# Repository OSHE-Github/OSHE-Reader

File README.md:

# **OSHE-Reader Spring 2026 Report**

Ian Mitchell, Riley Patterson, Owen Dodson, Ian Ranstadler, Alycia Greer  
---

# **Description**

OSHE-Reader is an open-source e-reader device capable of displaying text from the EPUB and PDF E-book file formats. This project’s goal is to create a cheaper alternative to products from companies like Amazon and Kobo. It will stay open to the public, using free and open source software like LVGL, Github, EEZ Studio and Arduino IDE, allowing more collaboration and easy uploading of books, compared to other e-readers that require workarounds to upload custom content.

# **Methodology**

### **Overview**

The design of the OSHE-Reader is loosely based on the previous work of Joey Castillo’s *The Open Book* \[1\] and atomic14’s *ESP32 Based ePub Reader* \[2\]. The former was designed as a very basic implementation of an e-reader, with the main goal of being easily manufacturable by an end-user. Unfortunately, this goal came at the expense of quality, with the design being stripped down to bare essentials, both on the hardware side, lacking a proper case, using AAA batteries, as well as the software side only supporting raw text file formats. Atomic14’s design incorporates much more complicated features, especially on the software side with .epub file parsing for standard e-book reading capabilities, however this design was not made for end users, is lacking a case, and has limited e-paper screen support. The OSHE-Reader attempts to solve problems in these prior open source e-readers by creating an open source e-reader with full functionality, principled design choices, and most importantly: a simple and consistent experience for an end user.

The OSHE-Reader’s design falls largely into three categories: electrical, firmware, and hardware. The design considerations of these three categories are discussed in further detail below.

### **Electrical**

#### **Battery**

In order to be a device capable of being used portably, the OSHE-Reader needed to use some form of battery, such that the device could store energy and be used while not directly plugged in. For this system, we chose lithium polymer (LiPO) batteries for their slim profile and ability to be recharged. The choice to use a LiPO battery to power the device provides the best features in energy storage density and internal recharging, though at the cost of increased complexity relative to consumer AAA batteries, which require less surrounding systems to function, though are bulkier, heavier, and need to be removed to be recharged.

In order to recharge our LiPO batteries, two systems are necessary: a method of power connection as a source of power from which the battery can be charged, and a charging integrated chip (IC) which can handle the complex recharging process.

#### **Battery Charging**

To handle the power connection system, we decided on using the existing USB-C port. This port provides a consistent, readily available connector that works with a variety of existing cables, such as those used for charging phones or plugging in peripheral devices like computer mice and keyboards. This USB-C port is currently only used for charging, and as such requires minimal components, while allowing the e-reader to consume up to 1.5A of current, well above the requirements of the device. This device’s USB-C port was designed with the USB Implementers Forum’s guidelines on USB-C devices in consideration, and should stand up to the requirements for certification \[3\], though that is not something this project will be doing.

Regarding the second system required for the chosen LiPO batteries, the BQ2057CSNTR from Texas Instruments was chosen as our battery charging IC. The BQ2057CSNTR is an older battery charging chip, but was chosen primarily for its package. Because the BQ2057CSNTR comes packaged as a SOIC-8, the IC can be hand-soldered, which greatly reduces the barrier of entry for end users attempting to create their own OSHE-Reader. This however poses additional challenges, as the BQ2057CSNTR is lacking in some features, most notably of which is the lack of a power path feature, which means that the BQ2057CSNTR cannot, on its own, support using a device while simultaneously charging. This issue can be circumvented with the addition of a load-sharing system \[4\]. With this load-sharing system, the OSHE-Reader can now be used while charging.

#### **Buck Converter**

The LiPO battery outputs a voltage of 3.7 volts, but our screen and microcontroller run on 3.3 volts. To make sure we would be able to run both devices safely, we decided to add a buck converter to the circuit. The buck converter we picked is the TPS5432. The primary factor behind this choice was its package size, similar to our choice with the battery charging IC. By allowing it to be easily hand-solderable, such as with the SOIC-8 packaging type, it keeps our device available to more at-home builders. This device also helps keep the other components safe, as when it's running, any voltage too high, around \~4.3 volts, will cause a break, and it will need to be reset, and any value less than \~3.3 volts also puts the device in the same state. This additional protection helps make sure the user will not accidentally fry any parts they are using.

#### **Microcontroller**

For the OSHE-Reader, a core processing unit is necessary to do the computation required for the parsing and displaying of e-books. Because our device is battery-powered, a lower power microcontroller greatly increases the lifespan of our device. We selected the ESP32-C6 to be a featureful, yet low-power device that is readily available for hobbyists. ESP-IDF and Arduino IDE support the ESP32-C6 so development would also be easier. Flash size was a factor in selecting a microcontroller and the C6’s 8MB flash memory would be able to hold screen buffers. Furthermore, the C6 has a lot of sleep modes to limit power consumption while idle. Deep sleep in particular will be useful for the device in an “off state” where it can still wake up or refresh the screen periodically.

#### **Micro SD Card**

In order to be able to upload files to the OSHE Reader, an SD card reader was needed to provide EPUB files to the device. For this purpose, an SD card reader slot was chosen for our design. We chose to use a Push-Push mechanism for our SD card reader, since that would allow easier removal of the SD card from the slot in our case design, allowing the user to simply push the card inwards again and have it pop out, clear of the case, rather than needing to grab the device and pull it outwards from the inside of the case.

#### **User Input**

As described below in the GUI and Case Design sections, the OSHE-Reader will have five buttons (4 directions, 1 select). Each of these buttons must be connected to a GPIO pin on the microcontroller. Each of the buttons is pulled down to ground, such that the buttons are active high.

#### **Display**

The most user-facing component of the electrical system of the OSHE-Reader is the display. There is an enormous number of choices for potential displays, however the unique use case of displaying black and white book pages, which change fairly infrequently, means e-readers are particularly suited to e-paper displays. E-paper display technology is a relatively new display technology that trades refresh speed and color density for extreme power efficiency. We chose a Waveshare 5.83” 648 x 480 pixel display with 1-bit color depth as our e-paper display. We chose this display primarily because of its general availability and documentation, additionally, Waveshare has an ESP32 e-paper display driver board, which we used to verify our screen. This e-paper display uses a 4-wire SPI connection which is easy to implement on the microcontroller, however the display requires high voltages to operate, and thus needs an external boost converter. For our implementation we looked at the Waveshare driver board’s open source schematics and implemented a similar option \[5\].

#### **Printed Circuit Board**

For the design of our Circuit board, we wanted the vast majority of components to be hand solderable on our board. For this reason, most of our components are surface mount with a size of 1206, which is on the larger side of surface mount components.

### **Firmware**

#### **Micro SD Card**

#### In order to read from and write to an SD card, we imported the arduino SD card library (SD.h), which provides low level functionalities. However, in order to extract compressed files from an epub (zip archive), we needed access to a posix-style file system. To solve this problem, we employed the arduino-posix-fs library \[6\], which provides stdio functions (notably fopen, fclose, fread, and fwrite) which emulate the stdio.h functions found in a unix operating system.

#### **User Input**

#### To give the microcontroller the ability to read user input we must first enter the Arduino IDE again. We will connect pins from the microcontroller to certain functions that we will use in the e-reader GUI. Using the library OneButton \[7\] by mathertel, we were able to successfully debounce the buttons for single-press applications. This library is promising for future long-press implementations, such as turning on/off the device. Explicit button labels in the GUI allow for the user input to move to a new screen directly as opposed to moving around the screen to select an option. The buttons are responsive for the user and LVGL.

#### **EPUB File Processing**

In order to process an EPUB file from a zip archive to formatted text, three main steps need to be taken. Firstly, the archives files need to be extracted and uncompressed, then the archive needs to be parsed using an xml parser to extract the structural information about the contents of the EPUB, then finally, a word wrapping algorithm can be applied to format the raw text into a single page worth of text.

##### **EPUB File Unzipping**

The first step in the processing of an EPUB file is the decompression and extraction of the contents of the EPUB. To do this, we needed a library that could handle not only the decompression, but also have the necessary extensions for the archive support.

Many libraries supported the simple compression and decompression algorithms of the zip format, but only the miniz library \[8\] had support for the archive extensions, which provide an API for viewing the individual files in an archive, extracting them individually, and decompressing them.

Unfortunately, this library’s archive functions required the inclusion of the stdio header, which typically provides file read and write functionality on an operating system, however, working within the Arduino ecosystem, we had no operating system or file system. Therefore, we had to use the previously mentioned arduino-posix-filesystem library. While this substitution appeared to be successful, overall the integration of miniz into an embedded platform was unsuccessful, with the library still failing to function as of the end of the semester.

##### **EPUB File Parsing**

#### Parsing an EPUB requires extracting information from a few key files. The container file gives the location of the contents file. The contents file gives metadata (author, title, book language), locations of pages as xhtml files, the table of contents, and the spine. The table of contents includes all the chapters and a unique id attached to each.

Using Expat, the XML parser chosen last semester for its functionality with limited memory/processing power, we can parse this chain of files to gather all the relevant information on a book. Using the chapter ids from the table of contents and header tags in XML, we can locate the start of new chapters, and begin parsing them based on the paragraph tags. 

As we extract paragraphs, they will be sent to the pagination algorithm in chunks to be formatted on the screen. As the paragraphs are sent, we can keep track of where we left off in a chapter to maintain a kind of bookmark, as well as making the pages smoother if you close and reopen a book.

##### **Pagination and Word Wrapping**

For displaying the book for the user to view, we need a way to format the text while keeping count of pages. By taking the paragraphs from the file and formatting them to break the section of text into lines and not cut off words, we used EEZ Studio to have textboxes that will automatically wrap the text and display the page the user is on.

#### **Display**

In order to display images to our e-paper display, we needed an appropriate driver to send commands and data to the e-paper controller board located on the display. Previously we had been successful in using our display’s provided firmware, however that code was poorly written and documented and was both missing features we needed, while having a lot of core functionality like SPI being written using basic GPIO pins rather than the onboard SPI hardware. In order to solve this problem the library was re-written, keeping only the core needed functionality such as: turning on, clearing, updating the image displayed, entering sleep mode, and turning off. This way, the library could be both smaller, saving space for the rest of the firmware, and also faster, by using the hardware SPI functions of our microcontroller rather than the GPIO pins.

#### **GUI Design**

The GUI design pivoted to using direct button to screen navigation. Due to the slow refresh rate of the screen, it was preferable to make one button press change a screen, instead of using a button press to navigate through moving menus. We wanted a simplistic and easy to navigate GUI to make the experience as smooth as possible. Explicit buttons help the user understand where a button press will go, eliminating ambiguity. Settings allow for more customization for the screen, such as dark mode. The library screen will be full of book selections and clicking a book will take you to the text in the file. The center button will have an explicit back button when applicable, taking the user to the previous screen they were at. We included marmot imagery to set up a recognizable, user-friendly “mascot” of sorts. 

#### **LVGL**

The Light and Versatile Graphics Library (LVGL) is an open source program/library that allows for easy GUI development. After discussing possible routes of GUI libraries we could use, we eventually settled on LVGL due to its documentation, compatibility with ESP32, and UI editor applications. EEZ studio was used to generate LVGL assets. EEZ studio allowed for easy implementation of groups, buttons, labels, and other custom actions. The design was created in a GUI that generates C code once settings were adjusted.

### **Hardware**

#### **Case Design**

To design the case we wanted to make sure it was optimized for as many people as possible. This can be difficult due to different hand sizes, but we tried to standardize it. To get feedback we created an initial case out of cardboard, and showed it to people asking them to fill out a google form. This allowed us to get feedback before we invested hours into an incorrectly designed case. Due to feedback, we slightly increased the size of the case, and added buttons to both sides of the case. This should mean that it is accessible for people both left and right handed, and that it sits comfortably in most people's hands. We kept all the buttons on the front of the screen (vs the side) because it keeps the electronic and case design simple, and from our feedback it is still easy to push with the thumb when the device is in standard operating condition. PLA and PETG were tested when printing the case design, both are suitable for the application \[11\].

#### **3D Model**

To house the device we decided to create a shell in Onshape, as it is an open source and relatively simple to use modeling software; for the situations that the user wanted to update the case. The model is split into 5 key parts, the front shell, back plate, battery holder, rocker buttons, and screen holder. The goal of the design is to create a case that has covered tactile buttons, ensuring a seamless look. The main center button will be a flush spring button built into the front panel. This design was partially inspired by an older nook button design. Due to ribbon cable location issues, the side buttons were changed to rocker buttons. The original plan of designing side buttons similarly to the center button proved impossible as there was no location where the buttons could exist without compromising the ribbon cable on the screen. The outcome was good, the separate print is not time or resource intensive and they feel great. All parts of the shell will be held together with M3 screws. By using screws instead of a snapping system, if the device gets dropped it will not split apart. Some feedback suggested a screw hole that does not travel through the entire back panel for structure so that change was made to the original design.

# **Progress in Previous Semester**

The past semester we started the schematic on the components for the PCB including USB-C Connector, Battery Charging, Buck Converter, Button Input, Display Connector, Micro SD Card Slot, and the Microcontroller. Testing the Buck Converter, Battery Charging, and the Microcontroller Input on breadboard to test the components to make sure the parts will work. On the software side we used the Arduino libraries to display the screen and LVGL to develop the GUI with an easy navigated menu. Looking into parsing and displaying an EPUB file on the e-reader. We also started to design a 3D printed case keeping in mind the button placement and how everything will be held in place.

# **Bill of Materials**

| Description | Part Number | Source | Unit Price | Qty | Cost |
| :---: | :---: | :---: | :---: | :---: | :---: |
| ESP32-C6 Devboard | 25723 | Waveshare | $7.29 | 1 | $7.29 |
| PCB | Rev 1 | JLCPCB | $35.40 | 1 | $35.40 |
| 4.22k Ohm Resistor | AC1206FR-074K22L | Digikey | $0.10 | 1 | $0.10 |
| 45.3k Ohm Resistor | RC1206FR-0745K3L | Digikey | $0.10 | 1 | $0.10 |
| 66.5k Ohm Resistor | RC1206FR-0766K5L | Digikey | $0.10 | 1 | $0.10 |
| 10k Ohm Resistor | RMCF1206FT10K0 | Digikey | $0.10 | 2 | $0.20 |
| 49.9 Ohm Resistor | TNPW120649R9BEEA | Digikey | $0.41 | 1 | $0.41 |
| 3.24k Ohm Resistor | RC1206FR-073K24L | Digikey | $0.10 | 1 | $0.10 |
| 5.1k Ohm Resistor | AC1206FR-075K1L | Digikey | $0.10 | 2 | $0.20 |
| 100k Resistor | RC1206FR-07100KL | Digikey | $0.10 | 8 | $0.80 |
| 1k Resistor | RMCF1206FT1K00 | Digikey | $0.10 | 1 | $0.10 |
| 8.2 nFarad Capacitor | CC1206JKNPOZBN822 | Digikey | $0.47 | 1 | $0.47 |
| 82 pFarad Capacitor | CC1206JRNPOBBN820 | Digikey | $0.19 | 1 | $0.19 |
| 10 nFarad Capacitor | C1206C103K2RECTU | Digikey | $0.18 | 1 | $0.18 |
| 470 pFarad Capacitor | VJ1206A471JXGTW1HV | Digikey | $0.14 | 1 | $0.14 |
| 22 uFarad Capacitor | CL31A226KAHNNNE | Digikey | $0.08 | 2 | $0.16 |
| 0.1 uFarad Capacitor | C1206C104K5RACTU | Digikey | $0.08 | 6 | $0.48 |
| 10 uFarad Capacitor | CL31A106KBHNNNE | Digikey | $0.08 | 3 | $0.24 |
| 4.7 uFarad Capacitor | CL31B475KAHNNNE | Digikey | $0.16 | 2 | $0.32 |
| 1u/50V Farad Capacitor | C3216X7R1H105K160DB | Digikey | $0.24 | 7 | $1.68 |
| PNP BJT | PZT751T1G | DigiKey | $0.63 | 1 | $0.63 |
| BQ2057CSNTR | BQ2057CSNTR | Digikey | $3.87 | 1 | $3.87 |
| IRF7326D2TRPBF | IRF7326D2TRPBF | Digikey | $0.63 | 1 | $0.63 |
| 2.2 uHenries Inductor | AIML-1206-2R2K-T | Digikey | $0.21 | 1 | $0.21 |
| TPS5432DDA | TPS5432DDA | Digikey | $0.96 | 1 | $0.96 |
| Push Buttons | PTS636SM43SMTR LFS | Digikey | $0.20 | 5 | $1.00 |
| MBR0530 | MBR0530 | Digikey | $0.31 | 3 | $0.93 |
| Sil308EDL | SI1308EDL-T1-GE3 | Digikey | $0.58 | 1 | $0.58 |
| 10 u/1A Henries Inductor | CC453232A-100KL | Digikey | $0.40 | 1 | $0.40 |
| 112L-TDA0 | 112L-TDA0 | Digikey | $3.44 | 1 | $3.44 |
| CUHZ5V6\_H3F Diode | CUHZ5V6,H3F | Digikey | $0.44 | 1 | $0.44 |
| PPTC Polyfuse | 0ZCJ0050FF2G | Digikey | $0.20 | 2 | $0.40 |
| Thermistor | B57550G1103F000 | Digikey | $3.11 | 1 | $3.11 |
| LED | HSMY-C110 | Digikey | $0.29 | 1 | $0.29 |
| 2k Ohm Resistor | RC1206FR-132KL | Digikey | $0.10 | 1 | $0.10 |
| JST Connector | S2B-PH-K-S | Digikey | $0.10 | 1 | $0.10 |
| USB-C Connector | 2171750001 | Digikey | $0.75 | 1 | $0.75 |
| Test Point | S1751-46R | Digikey | $0.24 | 20 | $4.72 |
| Ribbon Cable Connector | FH12A-24S-0.5SH(55) | Digikey | $1.65 | 2 | $3.30 |
| 6.8k Resistor | ERA-8AEB682V | Digikey | $0.24 | 2 | $0.48 |
| 0.47 Resistor | KDV12DR470ET | Digikey | $0.28 | 1 | $0.28 |
| 0.2 Ohm Shunt Resistor | WSL2512R2000FEA | Digikey | $0.65 | 2 | $1.30 |

## **E-Reader Cost Breakdown **
**

# **Tools Used**

| Category  | Item  | Part Number | Source | Cost |
| :---- | :---- | :---- | :---- | :---- |
| Hardware | Breadboard  | PRT-12615 | SparkFun Electronics | $7.75 |
|  | Multimeter  | 167 | Fluke | $260.00 |
|  | Oscilloscope  | DSOX2004A | Newark | $3306.90 |
|  | Solder Iron | Hakko FX888Dx | Equipment | $121.47 |
| Software | Google Slides | N/A | Google | Free |
|  | LVGL | N/A | LVGL LLC | Free |
|  | Arduino IDE | N/A | Qualcomm Technologies, Inc. | Free |
|  | EEZ Studio | N/A | Envox Experimental Zone | Free  |
|  | KiCAD | N/A | KiCAD | Free |
|  | OnShape | N/A | PTC Inc. | Free |

# **Part Assembly**

### **PCB**

The circuit schematic and Circuit Board were both designed using KiCAD, a free open source software for circuit and circuit board design. The PCB was designed to be hand solderable while also not taking up a lot of space within the case to allow for the battery to take up the rest of the available space. Doing it this way would allow consumers to hand solder boards without the need of solder paste or reflow oven, while the size would allow the device to keep a slimmer profile making it more comfortable to hold. To achieve this, most of the components were surface mounted with a package size of 1206\. These components were easily soldered with a standard soldering iron heated to 470 degrees centigrade. Some components were not available in the 1206 package size that we wanted so these parts were soldered using reflow techniques. 

Future revisions of the Circuit Board should focus on a redesign of the device to allow for a smaller board to be created. There was also a need to add a schottky diode to our BJT to prevent backfeeding through Resistor 5 to allow for our battery charger to receive the voltage it needs to function properly.

#### **Display Connector**

The Display connector needs to adapt a fine pitch FPC cable with 0.5mm pitch, thus the connector component also has a 0.5mm pin pitch. For this reason, the display connector was not hand soldered and was instead soldered using reflow techniques in the interest of saving time. This had varying levels of success as this caused the contacts to bridge. Attempts to remove the display connector were made, but resulted in the removal of pads and traces connected to it. On a second attempt, the display connector was soldered to the board with a mixture of reflow and hand soldering techniques. This attempt did not result in bridged contacts and the display connector could be used.

#### **Buck Converter**

The design for the buck converter was borrowed from a design made by Texas Instruments as it was a proven design that utilized most of the parts already implemented in the schematic. The buck converter was then isolated from other components on the board due to the noise it creates, with all other components being routed around it.

#### **SD Card Slot**

The SD card reader was also only available in a package size smaller than 1206, however it was bigger than the package size for the display connector. This does mean that the SD Card reader is hand solderable given enough time and patience. However, it was reflow soldered for the sake of time.

### **Case**

All case pieces must be 3D-printed, which includes the front panel, back panel, screen bracket, two side buttons, and the battery bracket. The case has been tested in both PLA and PETG, both are suitable \[11\]. To assemble, start by placing the PCB on the bottom standoffs of the rear panel, aligning them with the screw holes. Plug in the battery to the PCB and fit inside the battery bracket. Align the battery bracket with the top standoffs of the rear panel, facing the battery downwards. The PCB and battery bracket should lay somewhat flush with each other. Attach the screen to the PCB via the ribbon cable and put the screen in the screen bracket. Set the screen bracket on top of the four standoffs, aligning them with the screw holes. For the front panel, align the side buttons with the holes on the front case. Flip over the front case with your figures holding the buttons in place or set the buttons on top of the PCB, facing you. Finally, place the top panel on top of the rest of the assembly and use four M3x14mm screws to close the case. Screw in the screws until there is a resistance of it hitting the back of the rear panel. The back of the case should be flush with no screw protrusions.

# **Characteristic Data**

The above graph shows an example of our safe battery charging circuit. On the horizontal axis the duration of the charging cycle is displayed in minutes, and on the vertical axis, the battery’s voltage level. During a charging cycle, the battery charging chip will start the battery in current regulation mode, where a set amount of current (\~100mA for our design) is driven into the battery, once a voltage threshold is reached, the battery charger initiates the voltage regulation mode, where the charging voltage is instead held steady and the charging current gradually decreases (not pictured). Finally, after the charging current reaches a minimum threshold, all charging stops automatically to prevent overcharging, at which point the battery is fully charged.

# **References**

| \[1\] | GitHub \- atomic14/diy-esp32-epub-reader: ESP32 Based ePub Reader [https://github.com/atomic14/diy-esp32-epub-reader](https://github.com/atomic14/diy-esp32-epub-reader) |
| :---- | :---- |
| \[2\] | GitHub \- joeycastillo/The-Open-Book: The Open Book: Project Reboot [https://github.com/joeycastillo/The-Open-Book](https://github.com/joeycastillo/The-Open-Book)  |
| \[3\] | USB Type-C® Cable and Connector Specification Release 2.4 [https://usb.org/document-library/usb-type-cr-cable-and-connector-specification-release-24](https://usb.org/document-library/usb-type-cr-cable-and-connector-specification-release-24) |
| \[4\] | Designing A Li-Ion Battery Charger and Load Sharing System With Microchip’s Stand-Alone Li-Ion Battery Charge Management Controller [https://ww1.microchip.com/downloads/en/AppNotes/01149c.pdf](https://ww1.microchip.com/downloads/en/AppNotes/01149c.pdf) |
| \[5\] | E-Paper ESP32 Driver Board V3 Schematic [https://files.waveshare.com/wiki/E-Paper-ESP32-Driver-Board/E-Paper\_ESP32\_Driver\_Board\_V3.pdf](https://files.waveshare.com/wiki/E-Paper-ESP32-Driver-Board/E-Paper_ESP32_Driver_Board_V3.pdf) |
| \[6\] | Arduino POSIX Filesystem Library [https://github.com/pschatzmann/arduino-posix-fs](https://github.com/pschatzmann/arduino-posix-fs) |
| \[7\] | OneButton Button Press Library [https://github.com/mathertel/OneButton](https://github.com/mathertel/OneButton) |
| \[8\] | Miniz (z-lib replacement) Library [https://github.com/richgel999/miniz](https://github.com/richgel999/miniz) |
| \[9\] | ESP32: Guide for MicroSD Card Module using Arduino IDE [https://randomnerdtutorials.com/esp32-microsd-card-arduino/](https://randomnerdtutorials.com/esp32-microsd-card-arduino/) |
| \[10\] | \[ESP32 & LVGL\] How to Use a Button as an Input for UI Control\!: [https://www.youtube.com/watch?v=Lp2\_MLgs7d0](https://www.youtube.com/watch?v=Lp2_MLgs7d0) |
| \[11\] | PETG vs PLA vs ABS: 3D Printing Strength Comparison [https://ultimaker.com/learn/petg-vs-pla-vs-abs-3d-printing-strength-comparison/](https://ultimaker.com/learn/petg-vs-pla-vs-abs-3d-printing-strength-comparison/) |
| \[12\] | Texas Instruments Buck Converter design [https://www.ti.com/lit/ds/symlink/tps5432.pdf](https://www.ti.com/lit/ds/symlink/tps5432.pdf) |

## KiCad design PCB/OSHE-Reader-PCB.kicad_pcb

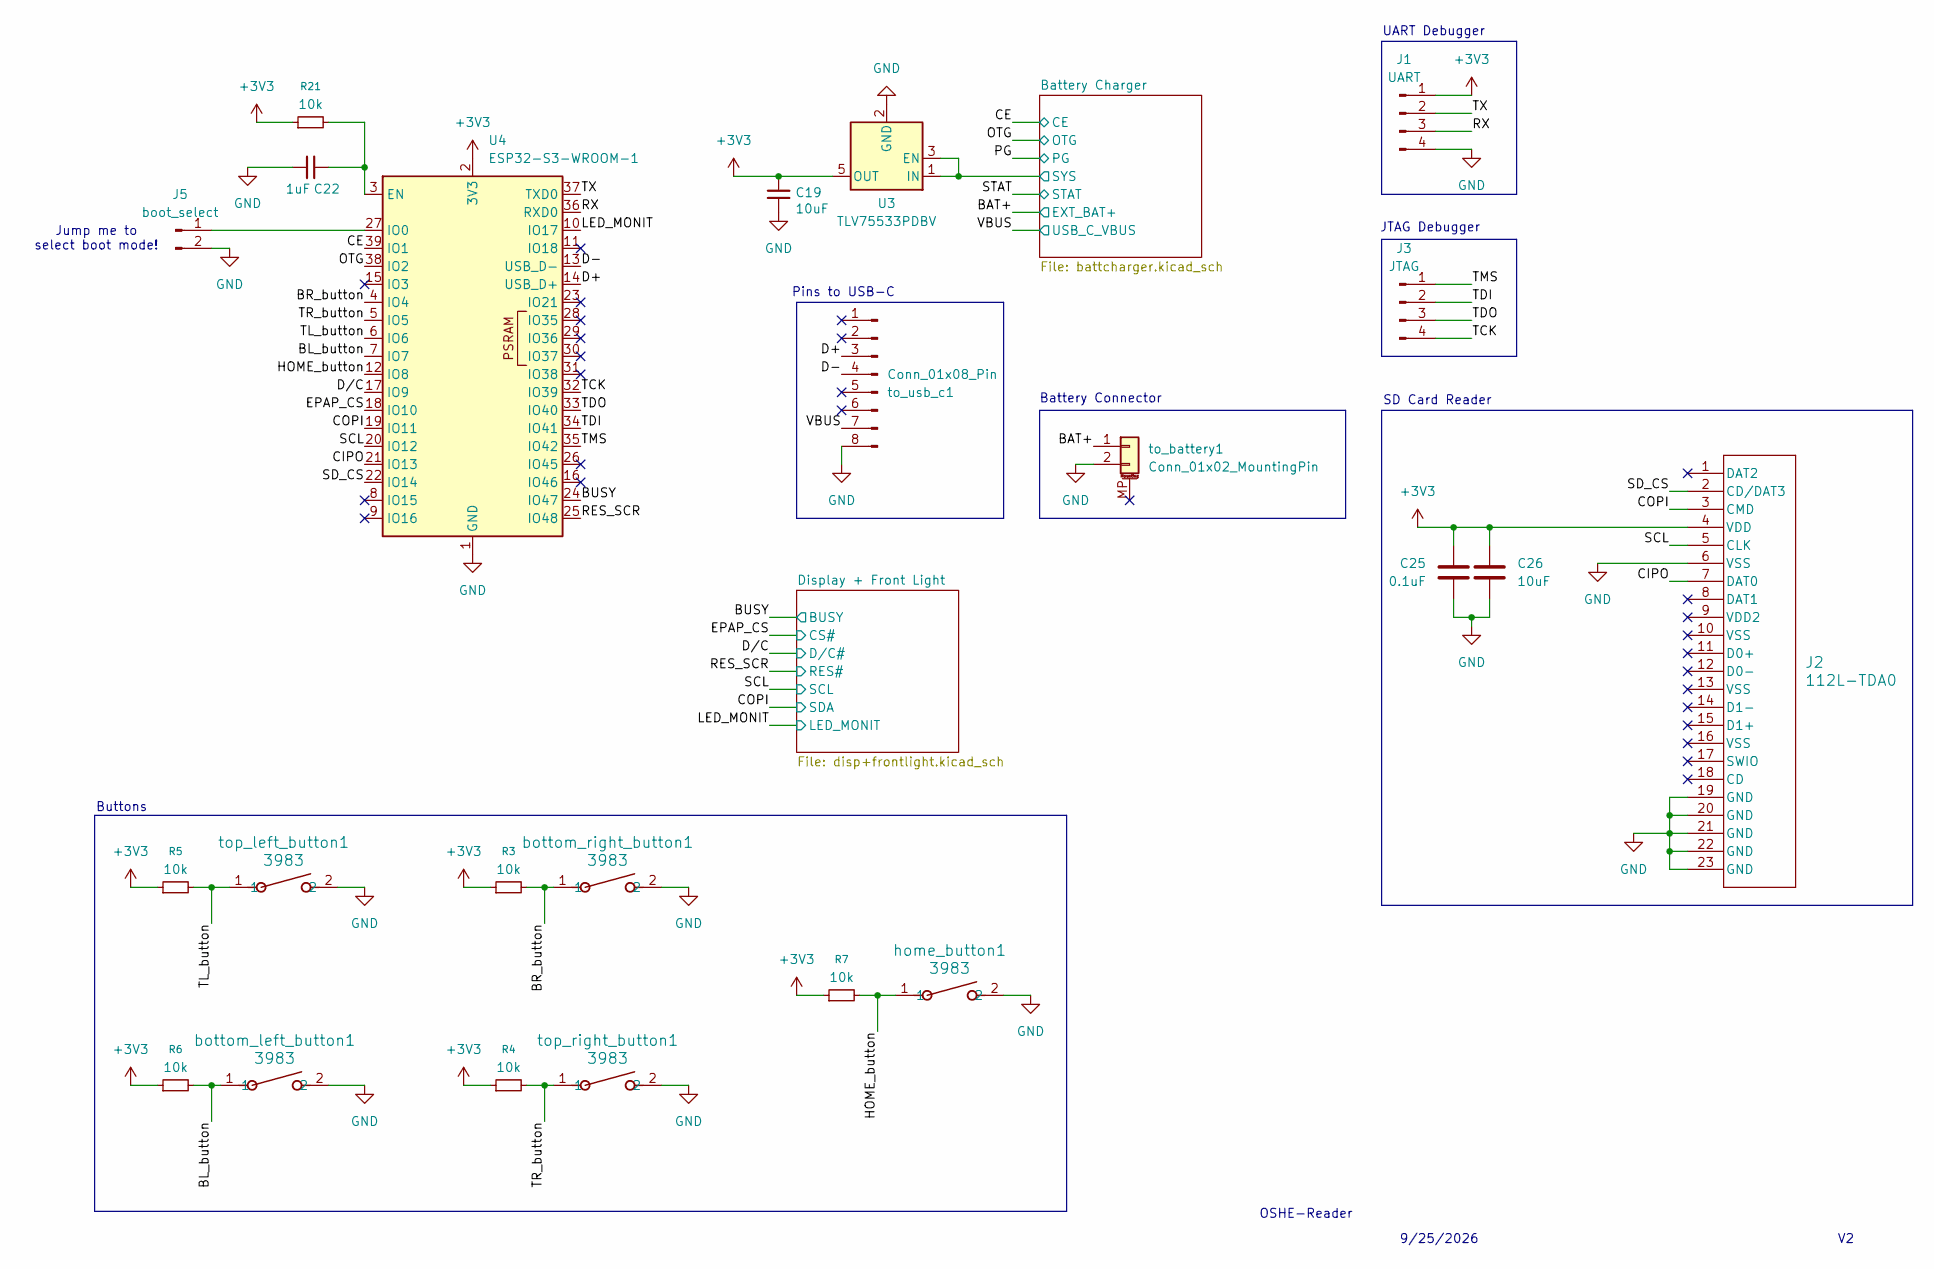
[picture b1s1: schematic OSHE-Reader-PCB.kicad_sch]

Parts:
C19: 10uF; C_1206_3216Metric_Pad1.33x1.80mm_HandSolder
C22: 1uF; L_1206_3216Metric_Pad1.22x1.90mm_HandSolder
C25: 0.1uF; C_1206_3216Metric
C26: 10uF; C_1206_3216Metric
J1: UART; PinHeader_1x04_P2.54mm_Vertical
J2: 112L-TDA0; CONN_112L-TDA0_ATT
J3: JTAG; PinHeader_1x04_P2.54mm_Vertical
J5: boot_select; PinHeader_1x02_P2.54mm_Vertical
R3, R4, R5, R6, R7, R21: 10k; R_1206_3216Metric_Pad1.30x1.75mm_HandSolder
U3: TLV75533PDBV; SOT-23-5
U4: ESP32-S3-WROOM-1
bottom_left_button1: 3983; SW_3983_ADA
bottom_right_button1: 3983; SW_3983_ADA
home_button1: 3983; SW_3983_ADA
to_battery1: Conn_01x02_MountingPin; JST_PH_S2B-PH-SM4-TB_1x02-1MP_P2.00mm_Horizontal
to_usb_c1: Conn_01x08_Pin; PinHeader_1x08_P2.54mm_Vertical
top_left_button1: 3983; SW_3983_ADA
top_right_button1: 3983; SW_3983_ADA

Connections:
+3V3: C19.1, C25.1, C26.1, J1.1, J2.4 (VDD), R3.1, R4.1, R5.1, R6.1, R7.1, R21.1, U3.5 (OUT), U4.2 (3V3); also elsewhere on the board
/BAT+: to_battery1.1; also elsewhere on the board
/BL_button: R6.2, U4.7 (IO7), bottom_left_button1.1
/BR_button: R3.2, U4.4 (IO4), bottom_right_button1.1
/BUSY: U4.24 (IO47); also elsewhere on the board
/Battery Charger/SYS: U3.1 (IN), U3.3 (EN); also elsewhere on the board
/CE: U4.39 (IO1); also elsewhere on the board
/CIPO: J2.7 (DAT0), U4.21 (IO13)
/COPI: J2.3 (CMD), U4.19 (IO11); also elsewhere on the board
/D+: U4.14 (USB_D+), to_usb_c1.3
/D-: U4.13 (USB_D-), to_usb_c1.4
/D/C: U4.17 (IO9); also elsewhere on the board
/EPAP_CS: U4.18 (IO10); also elsewhere on the board
/HOME_button: R7.2, U4.12 (IO8), home_button1.1
/LED_MONIT: U4.10 (IO17); also elsewhere on the board
/OTG: U4.38 (IO2); also elsewhere on the board
/RES_SCR: U4.25 (IO48); also elsewhere on the board
/RX: J1.3, U4.36 (RXD0)
/SCL: J2.5 (CLK), U4.20 (IO12); also elsewhere on the board
/SD_CS: J2.2 (CD/DAT3), U4.22 (IO14)
/TCK: J3.4, U4.32 (IO39)
/TDI: J3.2, U4.34 (IO41)
/TDO: J3.3, U4.33 (IO40)
/TL_button: R5.2, U4.6 (IO6), top_left_button1.1
/TMS: J3.1, U4.35 (IO42)
/TR_button: R4.2, U4.5 (IO5), top_right_button1.1
/TX: J1.2, U4.37 (TXD0)
/VBUS: to_usb_c1.7; also elsewhere on the board
GND: C19.2, C22.2, C25.2, C26.2, J1.4, J2.6 (VSS), J2.19 (GND), J2.20 (GND), J2.21 (GND), J2.22 (GND), J2.23 (GND), J5.2, U3.2 (GND), U4.1 (GND), U4.40 (GND), U4.41 (GND), bottom_left_button1.2, bottom_right_button1.2, home_button1.2, to_battery1.2, to_usb_c1.8, top_left_button1.2, top_right_button1.2; also elsewhere on the board
unnamed: J5.1, U4.27 (IO0)
unnamed: C22.1, R21.2, U4.3 (EN)

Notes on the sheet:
Battery Connector
Buttons
SD Card Reader
JTAG Debugger
9/25/2026
UART Debugger
Jump me to select boot mode!
OSHE-Reader
Pins to USB-C

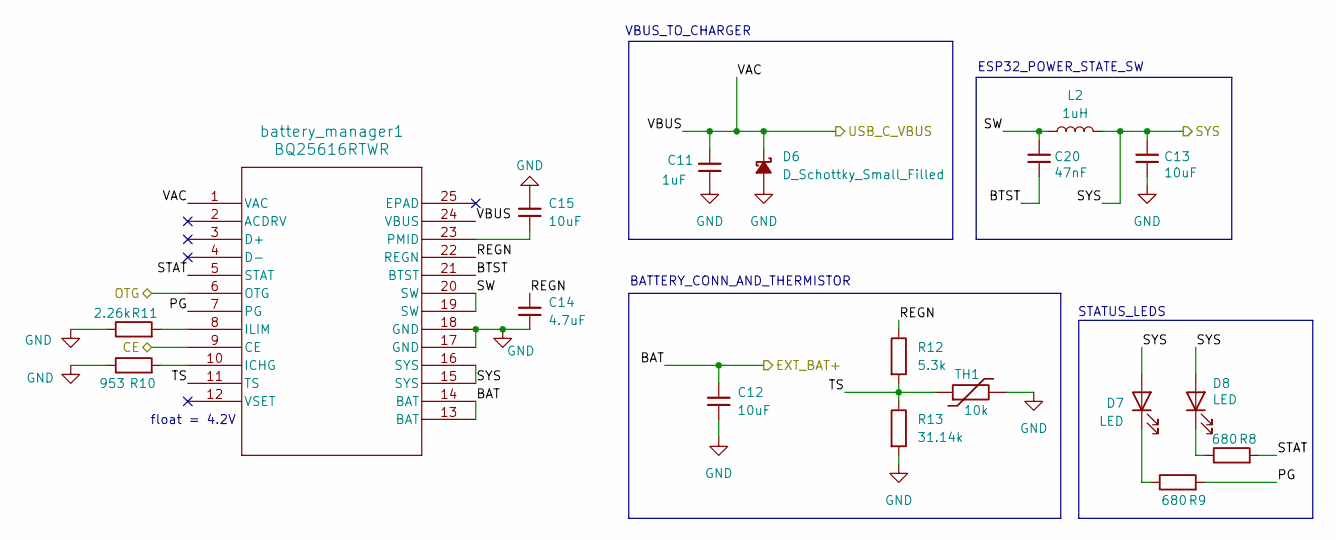
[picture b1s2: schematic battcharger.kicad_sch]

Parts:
C11: 1uF; C_1206_3216Metric_Pad1.33x1.80mm_HandSolder
C12, C13, C15: 10uF; C_1206_3216Metric_Pad1.33x1.80mm_HandSolder
C14: 4.7uF; C_1206_3216Metric_Pad1.33x1.80mm_HandSolder
C20: 47nF; C_1206_3216Metric_Pad1.33x1.80mm_HandSolder
D6: D_Schottky_Small_Filled; D_1206_3216Metric_Pad1.42x1.75mm_HandSolder
D7, D8: LED; PinHeader_1x02_P2.54mm_Vertical
L2: 1uH; L_1206_3216Metric_Pad1.22x1.90mm_HandSolder
R8, R9: 680; R_1206_3216Metric_Pad1.30x1.75mm_HandSolder
R10: 953; R_1206_3216Metric_Pad1.30x1.75mm_HandSolder
R11: 2.26k; R_1206_3216Metric_Pad1.30x1.75mm_HandSolder
R12: 5.3k; R_1206_3216Metric_Pad1.30x1.75mm_HandSolder
R13: 31.14k; R_1206_3216Metric_Pad1.30x1.75mm_HandSolder
TH1: 10k; PinHeader_1x02_P2.00mm_Vertical
battery_manager1: BQ25616RTWR; QFN24_RTW_TEX

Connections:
/BAT+: C12.1, battery_manager1.13 (BAT), battery_manager1.14 (BAT); also elsewhere on the board
/Battery Charger/BTST: C20.2, battery_manager1.21 (BTST)
/Battery Charger/PG: R9.2, battery_manager1.7 (PG)
/Battery Charger/REGN: C14.1, R12.1, battery_manager1.22 (REGN)
/Battery Charger/STAT: R8.2, battery_manager1.5 (STAT)
/Battery Charger/SW: C20.1, L2.1, battery_manager1.19 (SW), battery_manager1.20 (SW)
/Battery Charger/SYS: C13.1, D7.2 (A), D8.2 (A), L2.2, battery_manager1.15 (SYS), battery_manager1.16 (SYS); also elsewhere on the board
/Battery Charger/TS: R12.2, R13.1, TH1.1, battery_manager1.11 (TS)
/CE: battery_manager1.9 (CE); also elsewhere on the board
/OTG: battery_manager1.6 (OTG); also elsewhere on the board
/VBUS: C11.1, D6.1 (K), battery_manager1.1 (VAC), battery_manager1.24 (VBUS); also elsewhere on the board
GND: C11.2, C12.2, C13.2, C14.2, C15.1, D6.2 (A), R10.1, R11.1, R13.2, TH1.2, battery_manager1.17 (GND), battery_manager1.18 (GND); also elsewhere on the board
unnamed: D7.1 (K), R9.1
unnamed: D8.1 (K), R8.1
unnamed: R10.2, battery_manager1.10 (ICHG)
unnamed: R11.2, battery_manager1.8 (ILIM)
unnamed: C15.2, battery_manager1.23 (PMID)

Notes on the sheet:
VBUS_TO_CHARGER
ESP32_POWER_STATE_SW
float = 4.2V
STATUS_LEDS
BATTERY_CONN_AND_THERMISTOR

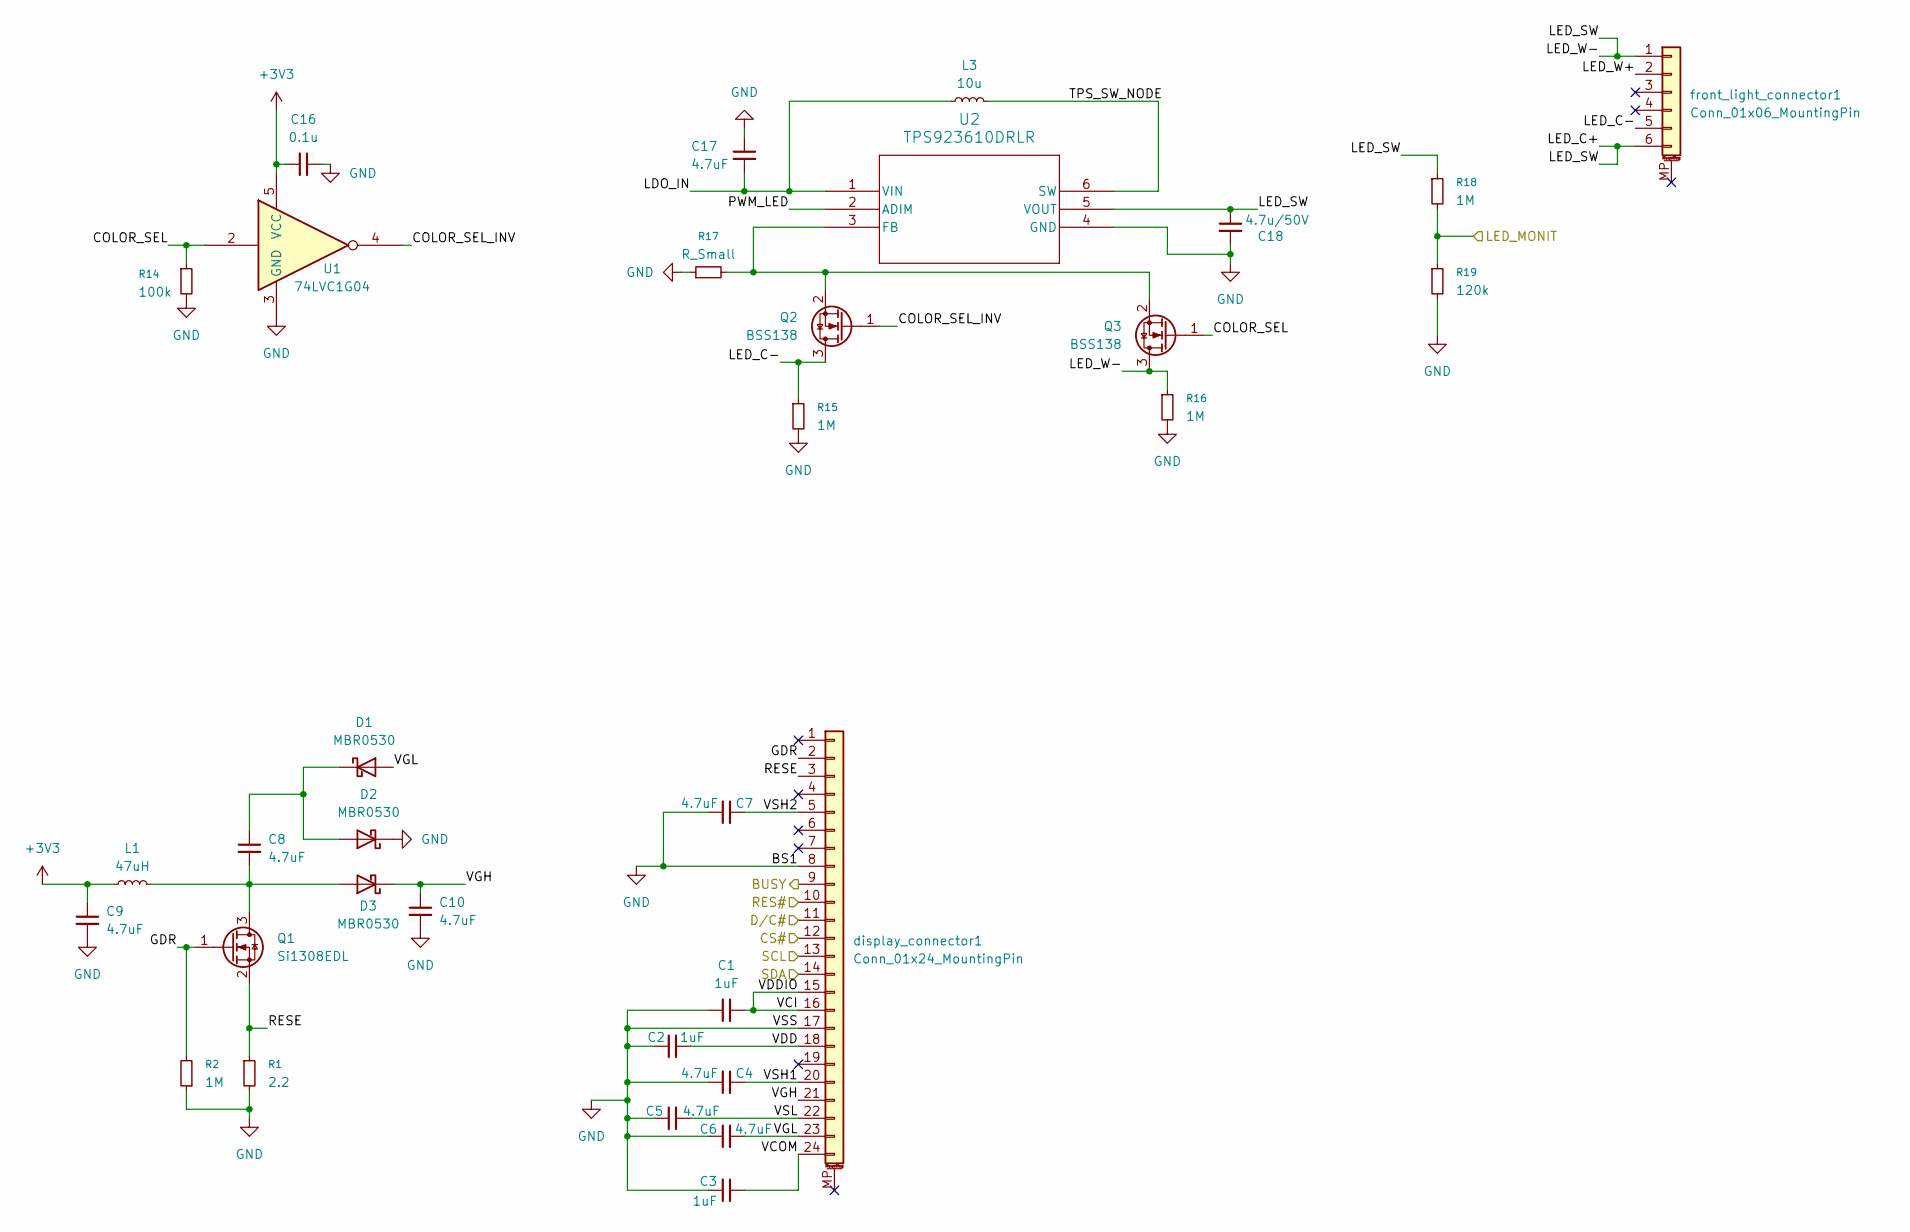
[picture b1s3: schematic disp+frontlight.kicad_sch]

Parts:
C1, C2, C3: 1uF; C_1206_3216Metric_Pad1.33x1.80mm_HandSolder
C4, C5, C6, C7, C8, C9, C10, C17: 4.7uF; C_1206_3216Metric_Pad1.33x1.80mm_HandSolder
C16: 0.1u; C_1206_3216Metric_Pad1.33x1.80mm_HandSolder
C18: 4.7u/50V; C_1206_3216Metric_Pad1.33x1.80mm_HandSolder
D1, D2, D3: MBR0530; D_1206_3216Metric_Pad1.42x1.75mm_HandSolder
L1: 47uH; L_1206_3216Metric_Pad1.22x1.90mm_HandSolder
L3: 10u; L_1206_3216Metric_Pad1.22x1.90mm_HandSolder
Q1: Si1308EDL; SOT-23_Handsoldering
Q2, Q3: BSS138; SOT-23_Handsoldering
R1: 2.2; R_1206_3216Metric_Pad1.30x1.75mm_HandSolder
R2, R15, R16, R18: 1M; R_1206_3216Metric_Pad1.30x1.75mm_HandSolder
R14: 100k; R_1206_3216Metric_Pad1.30x1.75mm_HandSolder
R17: R_Small; R_1206_3216Metric_Pad1.30x1.75mm_HandSolder
R19: 120k; R_1206_3216Metric_Pad1.30x1.75mm_HandSolder
U1: 74LVC1G04; SOT-23-5_HandSoldering
U2: TPS923610DRLR; SOT-563
display_connector1: Conn_01x24_MountingPin; Hirose_FH12-24S-0.5SH_1x24-1MP_P0.50mm_Horizontal
front_light_connector1: Conn_01x06_MountingPin; Hirose_FH12-6S-0.5SH_1x06-1MP_P0.50mm_Horizontal

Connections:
+3V3: C9.1, C16.1, L1.1, U1.5 (VCC); also elsewhere on the board
/BUSY: display_connector1.9; also elsewhere on the board
/COPI: display_connector1.14; also elsewhere on the board
/Display + Front Light/COLOR_SEL: Q3.1 (G), R14.1, U1.2
/Display + Front Light/COLOR_SEL_INV: Q2.1 (G), U1.4
/Display + Front Light/GDR: Q1.1 (G), R2.2, display_connector1.2
/Display + Front Light/LDO_IN: C17.1, L3.1, U2.1 (VIN)
/Display + Front Light/LED_C+: C18.1, Q3.3 (D), R16.1, R18.1, U2.5 (VOUT), front_light_connector1.1, front_light_connector1.6
/Display + Front Light/LED_C-: Q2.3 (D), R15.1, front_light_connector1.5
/Display + Front Light/LED_W+: front_light_connector1.2
/Display + Front Light/PWM_LED: U2.2 (ADIM)
/Display + Front Light/RESE: Q1.2 (S), R1.1, display_connector1.3
/Display + Front Light/TPS_SW_NODE: L3.2, U2.6 (SW)
/Display + Front Light/VCI: C1.2, display_connector1.15, display_connector1.16
/Display + Front Light/VCOM: C3.2, display_connector1.24
/Display + Front Light/VDD: C2.1, display_connector1.18
/Display + Front Light/VGH: C10.1, D3.1 (K), display_connector1.21
/Display + Front Light/VGL: C6.2, D1.2 (A), display_connector1.23
/Display + Front Light/VSH1: C4.2, display_connector1.20
/Display + Front Light/VSH2: C7.2, display_connector1.5
/Display + Front Light/VSL: C5.2, display_connector1.22
/D/C: display_connector1.11; also elsewhere on the board
/EPAP_CS: display_connector1.12; also elsewhere on the board
/LED_MONIT: R18.2, R19.1; also elsewhere on the board
/RES_SCR: display_connector1.10; also elsewhere on the board
/SCL: display_connector1.13; also elsewhere on the board
GND: C1.1, C2.2, C3.1, C4.1, C5.1, C6.1, C7.1, C9.2, C10.2, C16.2, C17.2, C18.2, D2.1 (K), R1.2, R2.1, R14.2, R15.2, R16.2, R17.1, R19.2, U1.3 (GND), U2.4 (GND), display_connector1.8, display_connector1.17; also elsewhere on the board
unnamed: C8.1, D1.1 (K), D2.2 (A)
unnamed: C8.2, D3.2 (A), L1.2, Q1.3 (D)
unnamed: Q2.2 (S), Q3.2 (S), R17.2, U2.3 (FB)

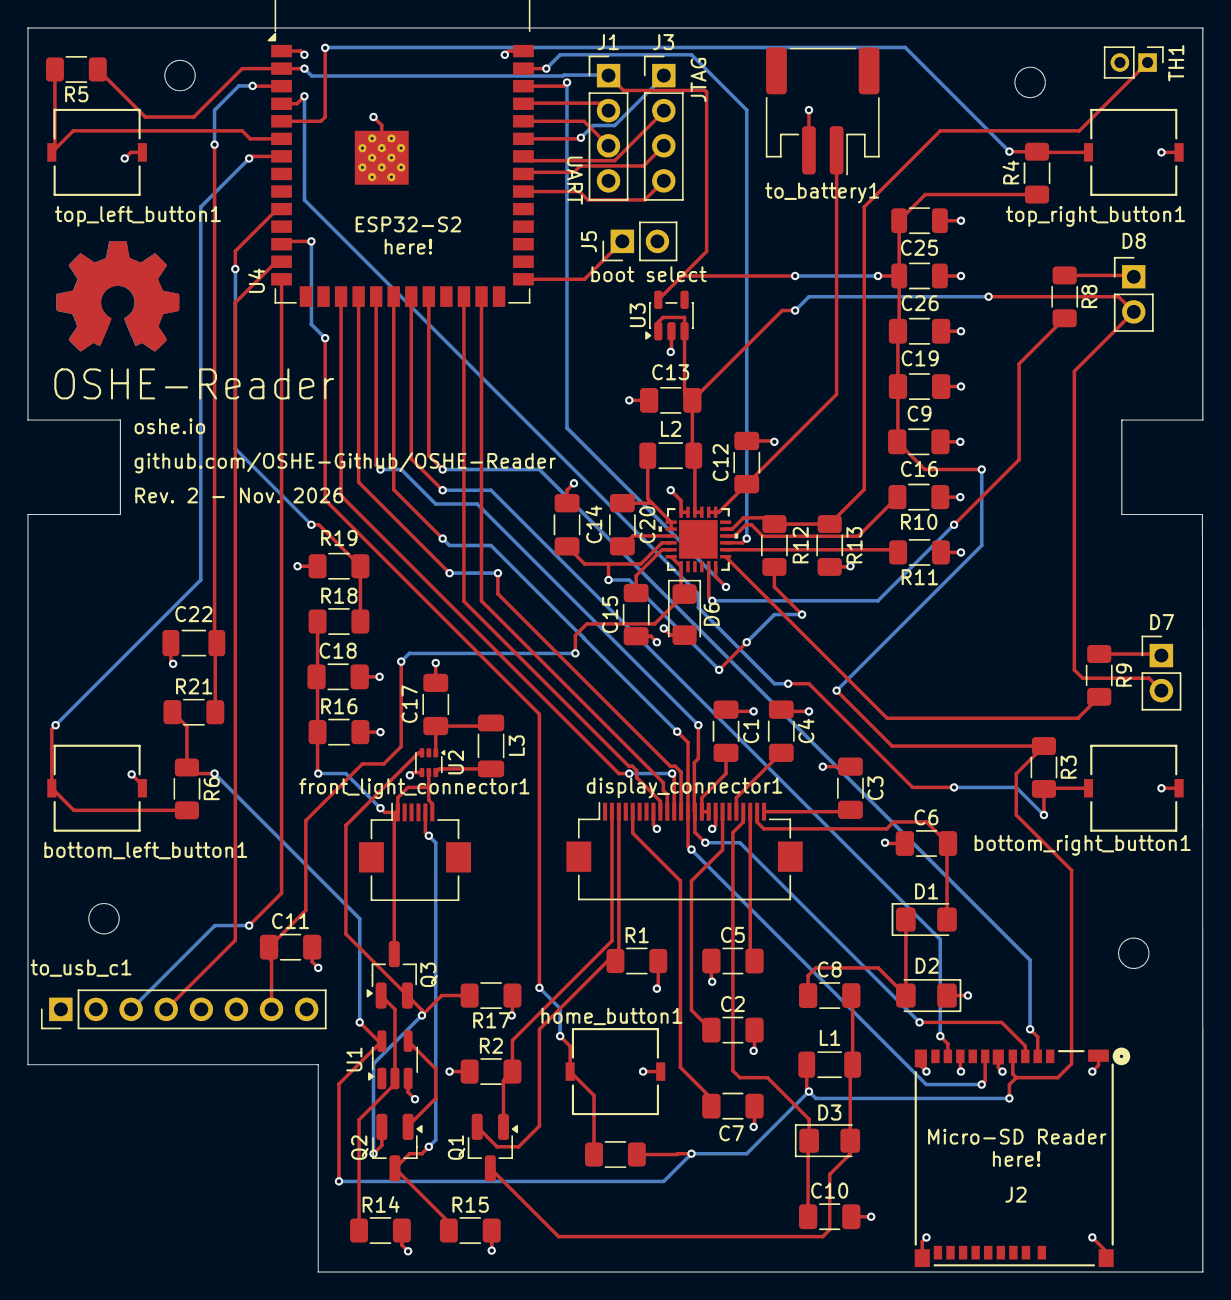
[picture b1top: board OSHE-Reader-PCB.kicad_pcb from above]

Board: 2 copper layers, 85.0 x 90.0 mm, 74 parts (0 on the bottom side), 61 nets.

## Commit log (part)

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2026-02-11 PCB Update
    Added OSHE logo and other labels and rand Design Check
2026-02-12 Replaced old FPC connector 3D model (.stl) with .stp for proper 3d rendering
2026-02-12 Added OSHE logo to backside of PCB, added info in bottom right of schematic
2026-02-12 Added a bunch of test points to schematic and pcb, hopefully not needed, but good to have :)
2026-02-12 Finishing touches with renaming some components and making auto BOM look cleaner
2026-02-12 PCB Update
    Shane looked at it :)
2026-02-12 Updated battery sense track length
2026-02-12 Deleted gerber files and created default PCB/out directory for gerber outputs (that is gitignored)
2026-02-13 update the HW interrupt so more
2026-02-13 Shuffled display connector around for fitting EPD ribbon cable position (also imported dxf for screen + bracket)
2026-02-15 Did a bunch of work: - Updated footprint libs with proper 3d models to fix models dissapearing on update from pcb - Updated footprint libs with better silkscreen for drc - Re-did ESP32-C6 Footprint t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
2026-02-16 A few minor changes
2026-02-18 Last updates for PCB order. Added revision number, fanicied logo, finished button positions, TODO: Blizzard T. Husky signature :P
2026-02-20 Added EEZ Studio Project
2026-02-20 Update Reader.eez-project
2026-02-20 Build test
2026-02-25 Moved around + Updated Case Files
2026-02-26 Updated EEZ studio design
2026-03-13 Remove unused action
2026-03-18 *finished* library for the epaper display, find at Firmware/EPD-Custom-Example
2026-03-20 New approach to parsing
    Using libxml2 for parsing, as opposed to expat. Currently going off tutorials (and imo better documentation).
2026-03-29 pushed unzip-w-posix-fs code so riley can work with it
2026-03-30 Updated with current firmware
2026-03-30 New file for parsing
    Off the original parser, this has a clearer idea and a little more implementation, up to parsing the toc. There are remnants of the old file that will be deleted or edited.
2026-03-30 Reverted PCB to old version, KiCad 10 made a new autosave directory to ignore
2026-03-30 Moved /Firmware to /Testing
2026-03-31 Check-off updates to main source code
2026-04-06 PCB and Schematic update
    added the Schottky diode to PCB and Schematic
2026-04-16 Minor fixes to PCB: schottky diode for battery charging and general battery charging routing fixes
2026-04-22 Update README.md with project report for spring 2026
2026-04-22 Update README.md final time for spring 2026
2026-04-22 minor formatting error
